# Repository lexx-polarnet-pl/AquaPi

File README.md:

# AquaPi

The aim of this project is to build Raspberry Pi controlled platform for aquarium management.

## Table of contents
* [General info](#general-info)
* [Screenshots](#screenshots)
* [Versions](#Versions)
* [Setup](#setup)
* [Features](#features)
* [Status](#status)
* [Inspiration](#inspiration)
* [Contact](#contact)

## General info
This project is licensed using GPL 2.0 version.
It's combination of hardware layer and software as well.
Structure of directories is following:

* Software - source codes of daemon and php web ui.
* Hardware - all hardware designs (created using KiCad).
* Doc      - place for documentation.

You can like it or not, but software is written (and documentation as well) in Polish language.

## Screenshots

## Versions
* Version 1.0 - still one and only stable version that was released.
* Version 2.0 - aka still in development phase - far more advanced than previous one, but also still not finished (but quite stable).

## Setup
Please see Doc directory if you wish to learn more about setup process.

## Features
List of features ready:
* Heating/cooling tank with different temperature settings between night and day.
* Light control with PWM usage to simulate sunrise/dawn.
* Recording of statistical data collected from sensors into database, and visualization on charts.
* Can be controlled using web browser, both on PC and mobile phone.
* Outputs controlled with timers with 1 second accuracy (nice for DIY feeders or fertilizers).

TODOs for future development:
* still some stuff to do with CO&#8322;.
* and probably more small staff to do.

## Status
Project is: in progress.

## Inspiration
This project was inspired by [Aquamat](https://github.com/musashimm/aquamat). 

## Contact
Created by [lexx](mailto:lexx@polarnet.pl) (https://lexx.polarnet.pl/) - feel free to contact me!
AquaPi is also having its own home page - see https://aquapi.polarnet.pl/

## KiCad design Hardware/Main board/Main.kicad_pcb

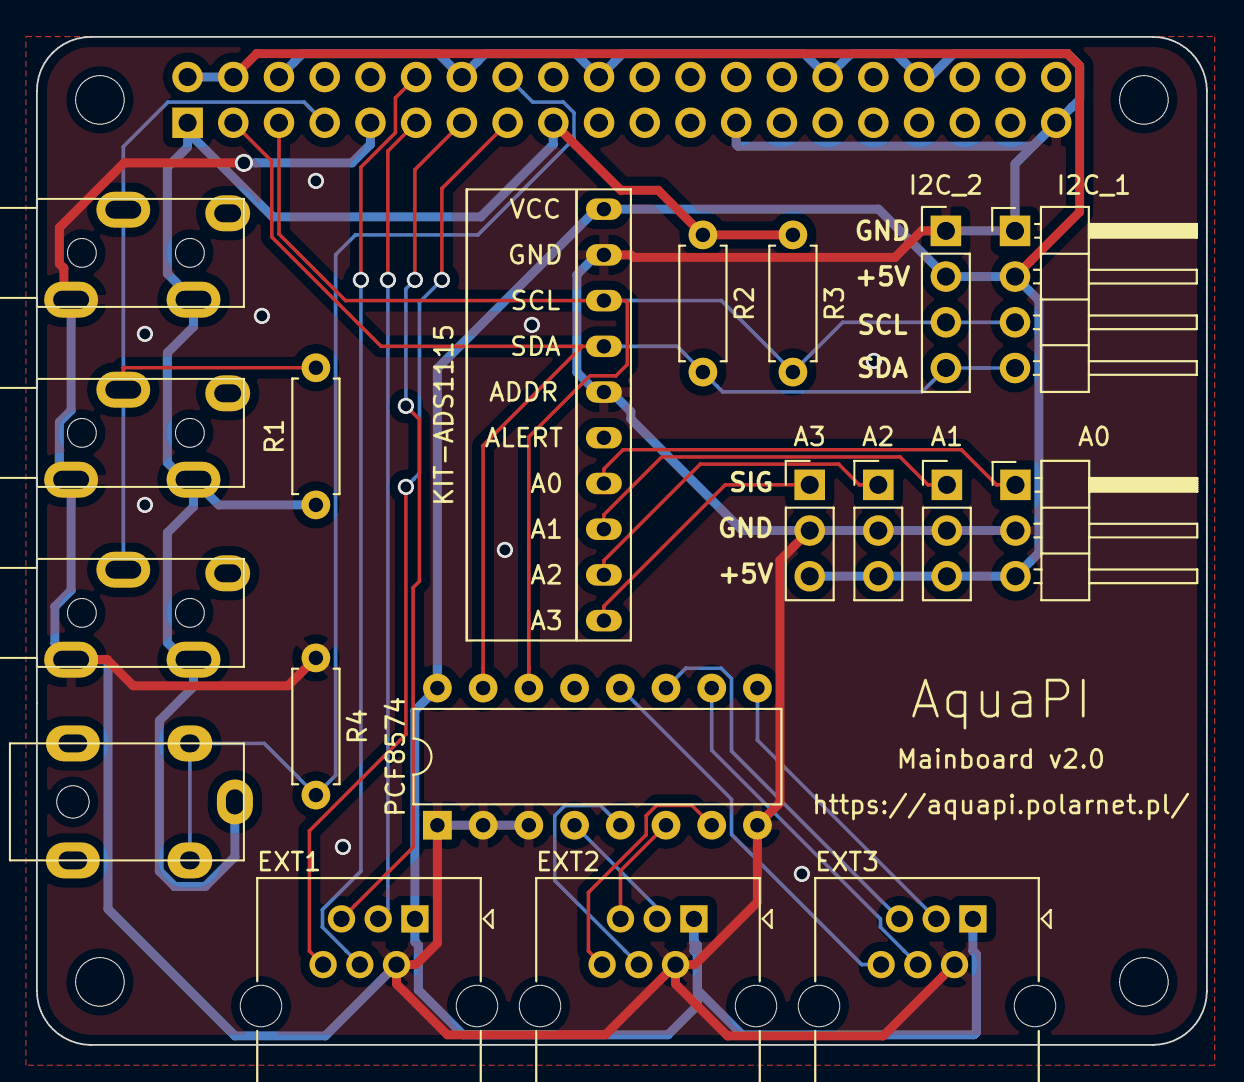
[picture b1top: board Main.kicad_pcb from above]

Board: 2 copper layers, 65.0 x 56.0 mm, 24 parts (1 on the bottom side), 23 nets.

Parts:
A0: ADC_A; Pin_Header_Angled_1x03_Pitch2.54mm
A1: ADC_B; Pin_Header_Straight_1x03_Pitch2.54mm
A2: ADC_C; Pin_Header_Straight_1x03_Pitch2.54mm
A3: ADC_D; Pin_Header_Straight_1x03_Pitch2.54mm
EXT1, EXT2, EXT3: RJ12; RJ25_Wayconn_MJEA-660X1_Horizontal
I2C_1: Conn_01x04_Male; Pin_Header_Angled_1x04_Pitch2.54mm
I2C_2: Conn_01x04_Male; Pin_Header_Straight_1x04_Pitch2.54mm
J1, J2, J3: PJ-327
J4: Barrel_Jack_Switch; DC-1GDC1.7_4.0K2
KIT-ADS1115: ADS1115IDGS; ADS1115-KIT
MK1, MK2, MK3, MK4: M2.5; MountingHole_2.7mm_M2.5
P1: Conn_02x20_Odd_Even; PinSocket_2x20_P2.54mm_Vertical
PCF8574: PCF8574; DIP-16_W7.62mm
R1, R2, R3, R4: 4,7k; R_Axial_DIN0207_L6.3mm_D2.5mm_P7.62mm_Horizontal

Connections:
+3V3: J1.3, J2.3, J3.3, J4.1, P1.1, P1.17, R1.1, R2.1, R3.1
+5V: A0.3, A1.3, A2.3, A3.3, EXT1.1, EXT2.1, EXT3.1, I2C_1.2, I2C_2.2, KIT-ADS1115.8, P1.2, P1.4, PCF8574.16
/GPIO2(SDA1): I2C_1.4, I2C_2.4, KIT-ADS1115.9, P1.3, PCF8574.15, R2.2
/GPIO3(SCL1): I2C_1.3, I2C_2.3, KIT-ADS1115.10, P1.5, PCF8574.14, R3.2
/GPIO4(GCLK): J1.2, J2.2, J3.2, P1.7, R1.2
/GPIO17(GEN0): EXT1.3, P1.11
/GPIO18(GEN1)(PWM0): EXT1.4, P1.12
/GPIO22(GEN3): EXT1.6, P1.15
/GPIO23(GEN4): J4.2, J4.3, P1.16, R4.2
/GPIO27(GEN2): EXT1.5, P1.13
GND: A0.2, A1.2, A2.2, A3.2, EXT1.2, EXT2.2, EXT3.2, I2C_1.1, I2C_2.1, J1.1, J2.1, J3.1, KIT-ADS1115.1, KIT-ADS1115.3, P1.6, P1.9, P1.14, P1.20, P1.25, P1.30, P1.34, P1.39, PCF8574.1, PCF8574.2, PCF8574.3, PCF8574.8, R4.1
unnamed: A0.1, KIT-ADS1115.4
unnamed: A1.1, KIT-ADS1115.5
unnamed: A2.1, KIT-ADS1115.6
unnamed: A3.1, KIT-ADS1115.7
unnamed: EXT2.3, PCF8574.4
unnamed: EXT2.4, PCF8574.5
unnamed: EXT2.5, PCF8574.6
unnamed: EXT2.6, PCF8574.7
unnamed: EXT3.3, PCF8574.9
unnamed: EXT3.4, PCF8574.10
unnamed: EXT3.5, PCF8574.11
unnamed: EXT3.6, PCF8574.12

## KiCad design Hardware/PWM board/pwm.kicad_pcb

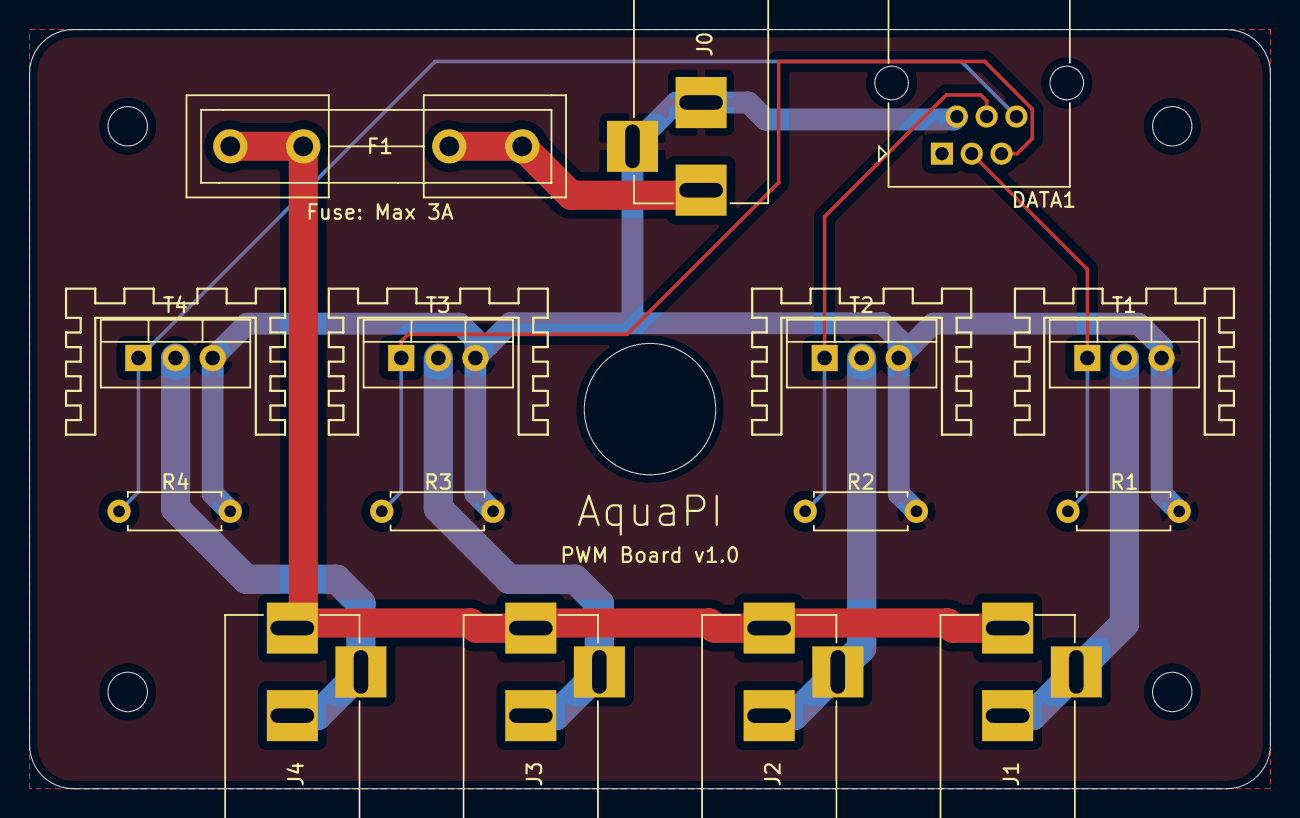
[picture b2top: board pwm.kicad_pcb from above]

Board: 2 copper layers, 85.0 x 52.0 mm, 19 parts (0 on the bottom side), 11 nets.

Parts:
DATA1: RJ12; RJ25_Wayconn_MJEA-660X1_Horizontal
F1: Fuse; Fuseholder5x20_horiz_open_inline_Type-I
H1, H2, H3, H4: MountingHole; MountingHole_2.7mm_M2.5
J0, J1, J2, J3, J4: Barrel_Jack_Switch; BARREL_JACK
R1, R2, R3, R4: 4,7k; R_Axial_DIN0207_L6.3mm_D2.5mm_P7.62mm_Horizontal
T1, T2, T3, T4: IRF520; TO-220-3_Vertical

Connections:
+12V: F1.1, J1.1, J2.1, J3.1, J4.1
/PWM1: J1.2, J1.3, T1.2
/PWM2: J2.2, J2.3, T2.2
/PWM3: J3.2, J3.3, T3.2
/PWM4: J4.2, J4.3, T4.2
/SIG1: DATA1.3, R1.2, T1.1
/SIG2: DATA1.4, R2.2, T2.1
/SIG3: DATA1.5, R3.2, T3.1
/SIG4: DATA1.6, R4.2, T4.1
GND: DATA1.2, J0.2, J0.3, R1.1, R2.1, R3.1, R4.1, T1.3, T2.3, T3.3, T4.3
unnamed: F1.2, J0.1

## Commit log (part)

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2013-11-11 poprawka warunku
2013-11-11 opis
2013-11-11 dostosowanie do nowej klasy DB
2013-11-11 zgodność ze starszą wersja PHP
2013-11-11 mozliwosc nie wyświetlania czujników na wykresie
2013-11-11 implementacja IPC
2013-11-11 Wczytywanie pozostałych parametrów daemona z ini
2013-11-11 poprawki wizualne
2013-11-12 dopasowanie do nowej klasy DB
2013-11-12 Update README.txt
    ort :P
2013-11-13 poprawa formatowania
2013-11-13 dodana lista autorów
2013-11-13 przepis na udaną (prawie) instalację
2013-11-13 fix na pustą baze
2013-11-14 work around na Strict Standards: Only variables should be passed by reference
2013-11-14 poprawka na wypadek braku timerów
2013-11-14 nie mozna było dodac sensora ktory nie miał byc pokazywany na wykresie.
2013-11-14 Update aquapi.sql
    rozszerzenie tabeli sensors
2013-11-14 oznaczanie jednego sensora jako master dla zgodnosci z demonem :(
2013-11-14 zmiana w demonie uwzgledniajaca tabele sensors
2013-11-15 poprawki zwiazane glownie z radzeniem sobie z brakiem danych w bazie
2013-11-15 porządki i zmiana nazewnictwa wyjść
2013-11-15 zapomniany commit
2013-11-16 dodane 2 funkcje pomocnicze
2013-11-16 nowy konfig
2013-11-17 Zaczątki dokumentacji
2013-11-17 przystosowanie strony konfiguracyjnej do nowej bazy + przebudowa
2013-11-18 kolejne poprawki stabilności
2013-11-19 zmiany w dokumentacji
2013-11-19 świerzo wygenerowana dokumentacja
2013-11-19 usunięcie zbędnych fragmentów RelayBoard
2013-11-19 Zmiany w about
2013-11-19 Ujednolicanie WebUi
2013-11-20 sprawdzanie poprawnego odczytu sensorów. błedne odczyty są odrzucane, a zdarzenie logowane
2013-11-20 poprawa drobnych błędów
2013-11-20 poprawki na liczne PHP Notice, poprawka demona, poprawka na brakujący podsystem 1wire.
2013-11-20 memmory leak fix
2013-11-22 2 formatki dodawania timerów.
2013-11-22 poprawka wysypujacego sie demona
2013-11-23 Dodana możliwość zabezpieczenia webui hasłem
2013-11-23 zbędny plik
2013-11-24 demon loguje temperatory z czujnika dummy, poprawka aktualizacji sensorów, temperatury nocne. poprawione duperele.
2013-11-25 ciąg dalszy dokumentacji
2013-11-25 Tu nie jest wymagany
2013-11-25 zmiana
2013-11-26 jeszcze zmiany
2013-11-26 poprawki po merge
2013-12-28 dostosowanie do nowego formatu bazy
2013-12-28 enable $id$ tag
2013-12-29 Podstawowa obsługa timerów (czasowych) jeszcze bez dni tygodnia
2013-12-29 poprawki w UI oraz rozbudowa IPC - statusy urządzeń są teraz czytane bezpośrednio z daemona bez użycia bazy
2013-12-30 konwersja na UTF8
2013-12-30 Raportowanie stanu nieustalonego
2014-01-02 zmiana roku
2014-01-08 Zaczątek obsługi dni tygodnia
2014-01-23 naprawa nie działajacego przełaczania sekcji w ustawieniach
2014-01-24 aktywacja zakładki kamery
2014-01-25 poprawka dashboard o brakujace sekcje. opcja w ini do ich właczania
2014-01-26 Poprawa ustawień czujników, mozliwosc wyłaczenia czujnika, opcja w konfiguracja wskazujaca czy demon jest lokalny czy zdalny, korekta dashboard.
2014-02-02 id + drobne poprawki
2014-02-11 poprawka master sensora
2014-02-13 poprawki czasu, opisów i jakiejs drobnicy.
2014-03-01 Drobna poprawka nagłówka
2014-03-01 Dodany viewport - nie zmniejszaj ekranu na komórkach
2014-03-01 dopiski w dokumentacji
2014-03-01 zwiększenie limitu failcount
2014-03-02 Lekkie poprawki pod urządzenia mobilne, chociaż jeszcze długa droga...
2014-03-02 Eksperyment z layoutem
2014-03-15 poprawka zapisywania nowych sensorów do bazy.
2014-03-15 uruchomienie wykresów. brak wsparcia dla brakujacych danych. (trzeba by generowac null przy wyciaganiu danych)
2014-03-15 poprawka przedrostka dummy
2014-03-15 Update aquapi.c
    literówka
2014-03-15 reload_freq jest obsługiwane
2014-03-15 korekta zapytania
2014-03-16 poprawa wyswietlania logów, czyszczenie logów, nowa opcja w konfigu, zmiana nazwy pliku ini z konfiguracją.
2014-03-16 poprawka na brakujaca opcje aby nie czysciło całych logów
2014-03-16 zmiana ikonek
2014-03-16 Update aquapi.ini
    opcja kamera
2014-03-16 dopasowanie do nowego konfiga
2014-03-16 wyłaczanie kawałków kodu zgodnie z opcjami w ini
2014-03-16 Update tcpip.c
    config.interface => config.host
2014-03-16 Update aquapi.c
    bind-address, bind-port
2014-03-16 Update tcpip.c
    _
2014-03-16 Update aquapi.c
    _
2014-03-16 Update inifile.c
    _
2014-03-16 Update aquapi.ini
    _
2014-03-16 wartości domyślne
2014-03-16 negowanie wyjść
2014-03-16 usunięcie $Id
2014-03-16 dodano xml2array
2014-03-16 Delete aquapi2.ini
    nie potrzebny
2014-03-16 dopasowanie ustawien do ipc->1wlist
2014-03-16 ustandaryzowanie nazwy templatki
2014-03-16 kolorowanie i lepsze opisy dla devel
2014-03-16 fix, ale brzydki
2014-03-17 mozliwosc usuniecia czujników dummy
2014-03-17 poprawka wizualna
2014-03-17 Usunięcie zbędnych $Id$
2014-03-18 lepsza obsługa rb
2014-03-18 usuniecie usera
2014-03-18 usunięcie usera
2014-03-18 obsługa czujników systemowych
2014-03-18 aktualizacja struktury DB
2014-03-18 cleanup i dodanie komendy aquapi:sysinfo
2014-03-18 poprawki
2014-03-19 poprawki konfiguracji gpio, zmina zrodla danych dashboarda
2014-03-19 Dodanie obsługi korekty temp. nocnej
2014-03-19 zapis stanu wyjść
2014-03-19 usunięte już zrobione
2014-03-19 kolejne zrobione
2014-03-19 Wycięcie warningów
2014-03-20 wartości nieokreślone z czujników są zapisywane w bazie jako null
2014-03-21 obsługa wyłaczonych czujników + opis typów wejsc RB
2014-03-21 przeróbka dashboard
2014-03-21 dodana obsługa taga <NOBR></NOBR>
2014-03-22 wykresy przekaźników, wyłaczanie przekaźników w konfiguracji, rożne drobne poprawki.
2014-03-22 porawka tytułu
2014-03-22 fix tabeli
2014-03-22 poprawka Jarka
2014-03-22 początek obsługi manualnego włączania wyjść w demonie
2014-03-31 dodanie obsługi pseudoczujnika rpi:system:txtfile
2014-03-31 poprawka na odczyt 85stopni z DSa
2014-03-31 plugin odczytujacy pogode :)
2014-04-01 dodane identyfikatory sensorów
2014-04-01 dodanie 2 tabeli
    dodanie tabeli jednostek oraz relacji jednostek z interfejsami
2014-04-01 dodanie konfigurowalnych jednostek dla sensorów
2014-04-05 drobne fixy
2014-04-05 poprawka symbolu jednostki
2014-04-06 przeniesienie pluginów
2014-04-06 plugin weather.php uzywa danych z pliku ini i bazy.
2014-04-06 poprawka pluginu
2014-04-06 https://github.com/lexx-polarnet-pl/AquaPi/issues/21
    sensor głowny wyswietla sie na dashboard
2014-04-06 pwm w UI
2014-04-06 trigery pwm w UI
2014-06-16 Update aquapi.sql
    dodanie nowej tabeli
2014-06-16 zmiana sposobu kasowania
2014-06-29 poprawka zapisywania kalendarza. sekcja ustawienien urzadzenia wyswietla sie na podstawie właczonego/wyłaczonego urzadzenia, a nie na podstawie istnienia interfejsów tego urzadzenia.
2014-06-29 zmiana sposobu prezentacji timestampów
2014-06-29 dodanie kalendarza i jego obsługi
2014-06-29 Update aquapi.sql
    db_version fix
2014-06-30 poprawka na dirty hack
2014-07-01 poprawa zdarzen z kalendarza na dashboardzie
2014-07-02 zapomniany plik z upgradem
2014-07-02 kolorowanie komunikatów z kalendarz, odczyt s/n płyty rpi.
2014-07-02 dodanie opcji właczania i wyłaczania nowych sekcji/pluginów
2014-07-04 mod bazy pod zatwierdzanie zdarzeń
2014-07-04 to też powinno być opcjonalne
2014-07-05 dodany tip
2014-07-05 demon nie powinien się wywalać na systemach innych niż raspi przy próbie użycia GPIO
2014-07-06 na -O3 segfaulci na i386, piwo temu kto mi powie czemu
2014-07-06 zmniejszenie czasu oczekiwania na zmianę stanu interfacu + poprawa obsługi w UI
2014-07-06 poprawka formatu daty na bardziej czytelną
2014-07-07 usunięte zbędne dzielenie
2014-07-07 wizualizacja trybu auto i ręcznego
2014-07-07 Pokazywanie wszystkich wyjść w jednej tabelce
2014-07-08 negowanie
2014-07-08 negowanie było w złym miejscu
2014-07-09 todo jest teraz wissues na githubie
2014-07-13 podejście do tematu jak wyświetlać możliwe do ustawienia wejścia/wyjścia
2014-07-21 nieco inne dodawanie urządzeń
2014-07-22 poprawka na wejścia fully_editable_address (czyli np. plik tekstowy)
2014-08-01 Dodana (wstępna bo czekam na sondę) obsługa modułu miniPh (pomiar pH) oraz wyczyszczenie i poprawa obsługi expanderów i2c opartych o pcf8574
2014-08-01 Poprawki w obsłudze i2c
2014-08-01 wzmianka o i2c
2014-08-01 Przekompilowana dokumentacja
2014-08-01 Jak doprecyzować o co pytamy
2014-08-02 Przepisana reszta na libxml
2014-08-03 Teraz porty GPIO też mogą być wejściami
2014-08-03 demon mówi że GPIO może być też input
2014-12-27 Test nowego podejścia
2015-01-04 Kolejne dodatki
2015-01-05 początki zapisów do bazy
2015-01-06 ciąg dalszy prac
2018-04-06 zmiany w statystykach
2018-04-07 charts cleanup
2018-04-07 poprawki w CSS
2018-04-10 zmiana ilości logów z 30 na 100 jednocześnie na ekranie
2018-04-10 zaczątek możliwoścu ustawiania koloru przy interface
2018-04-13 nowe ikonki i zmiany w listach
2018-04-13 kolor wykresu zależy od ustawień w bazie
2018-06-05 robi się ładniej i ładniej
2018-12-02 ostatnie zmiany, głównie przejście z mysql na mysqli
2018-12-03 zmiany w pwm
2018-12-03 jeszcze kilka zmian w pwm
2018-12-07 kasacje
2018-12-08 czyszczenie kodu + przywrocenie niektorych plikow
2018-12-09 nie pokazuj bledow
2018-12-15 zmiany w timerach i ikonkach
2018-12-23 kolejne zmiany w ui + wsparcie dla jednostek
2019-01-01 poprawiona paginacja
2019-12-27 nowe readme
2019-12-27 zmiana układu na dashboard
2019-12-28 poprawka w jednostkach i odswierzanie ajax co 1 sec
2019-12-28 poprawiona konwersja liczb oraz odświerzanie co sekundę
2019-12-29 drobne zmiany
2019-12-30 dodanie funkcjonalności nawożenia co2 oraz kalibrowania sondy pH
2019-12-31 nowy screanshot
2019-12-31 ikonki przy urządzeniu są teraz we wszystkich menu
2020-01-02 dodanie opisu podłączenia urządzeń w dokumentacji
2020-01-02 dodany link do strony domowej aquapi
2020-01-05 czyszczenie kodu
2020-01-05 dalsze czyszczenie kodu
2020-01-06 nowy zrzut sql z aktualną strukturą bazy
2020-01-06 dalsze czyszczenie kodu i optymalizacja danych debug
2020-01-06 aktualizacja aquapi.ini do aktualnych danych
2020-01-06 drobne zmiany pod nowe raspi
2020-01-06 aktualizacja rozdzialu o instalacji aquapi
2020-01-13 zmiany w obsłudze mostka
2020-01-15 żegnamy brzydkie delay, witamy wywołanie sygnału co sekundę jako alarm
2020-02-24 kolejne zmiany w co2 (histereza)
2020-02-24 parametry wody
2020-02-25 wracamy do loop i delaj, sygnały nie wypaliły?
2020-02-28 poprawka w zapisywaniu statystyk
2020-02-29 dodanie opcji konfiguacji histerezy przy nawożeniu co2
2020-02-29 poprawa liczenia średniej pomiarów z sondy pH
2020-02-29 sysinfo jest odświerzane ajaxem
2020-03-01 poprawki w sterowaniu co2
2020-03-01 dodany scenariusz zachowania na wypadek awarii czujników
2020-03-01 nowa ikonka
2020-03-07 zmiana w pokazywaniu kolejności urządzeń na ekranie konfiguracji
2020-03-07 poprawki w ajax refresh
2020-04-19 nowsza wersja wiringpi
2020-04-19 przymiarki do obsługi ads1115
2020-04-20 dalsze zmiany
2020-04-20 zapomniany dwukropek
2020-04-20 zmiana w nazewnictwie pinów mostka ADC
2020-04-20 nowe jednostki
2020-04-25 literówki (poprawka)
2020-04-25 dodanie ADS1115 do dokumentacji
2020-05-01 skasowanie starych wersji płytek
2020-05-01 nowa płyta główna
2020-05-01 Poprawki w płycie głównej
2020-05-03 ominięcie problemu wyświetlania surowych wartości na UI przy pH
2020-06-14 nowy projekt sprzętu
2020-06-18 wielopoziomowe menu
2020-06-19 Skasowanie alarmów z modułu temp, i zrobienie alarmów uniwersalnych, możliwych do ustawienia dla każdego wejścia
2020-06-20 dwie nowe tabele
2020-06-20 dodanie notyfikacji na maila
2020-06-20 drobne zmiany w dokumentacji
2020-06-21 notyfikacje generują się nie częściej niż co 10 min, zapobiega "zalewaniu" błędami logów
2020-06-25 znowu można wybrać sondę co2
2020-07-01 poprawka wizualna wykresu kalibracyjnego
2021-12-30 jack 3,2 a nie 2,5
2022-01-06 Dodana obsługa pca9685
2022-01-06 Dodane zdjęcia zlożonego PWM board
2022-01-06 ignore .htaccess
2022-01-06 aktualizacja chart.js
